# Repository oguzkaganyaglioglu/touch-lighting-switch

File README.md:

# touch-lighting-switch
### Inspect the circuit and decide for yourself whether to use it or not.
### I am not responsible for any damage.

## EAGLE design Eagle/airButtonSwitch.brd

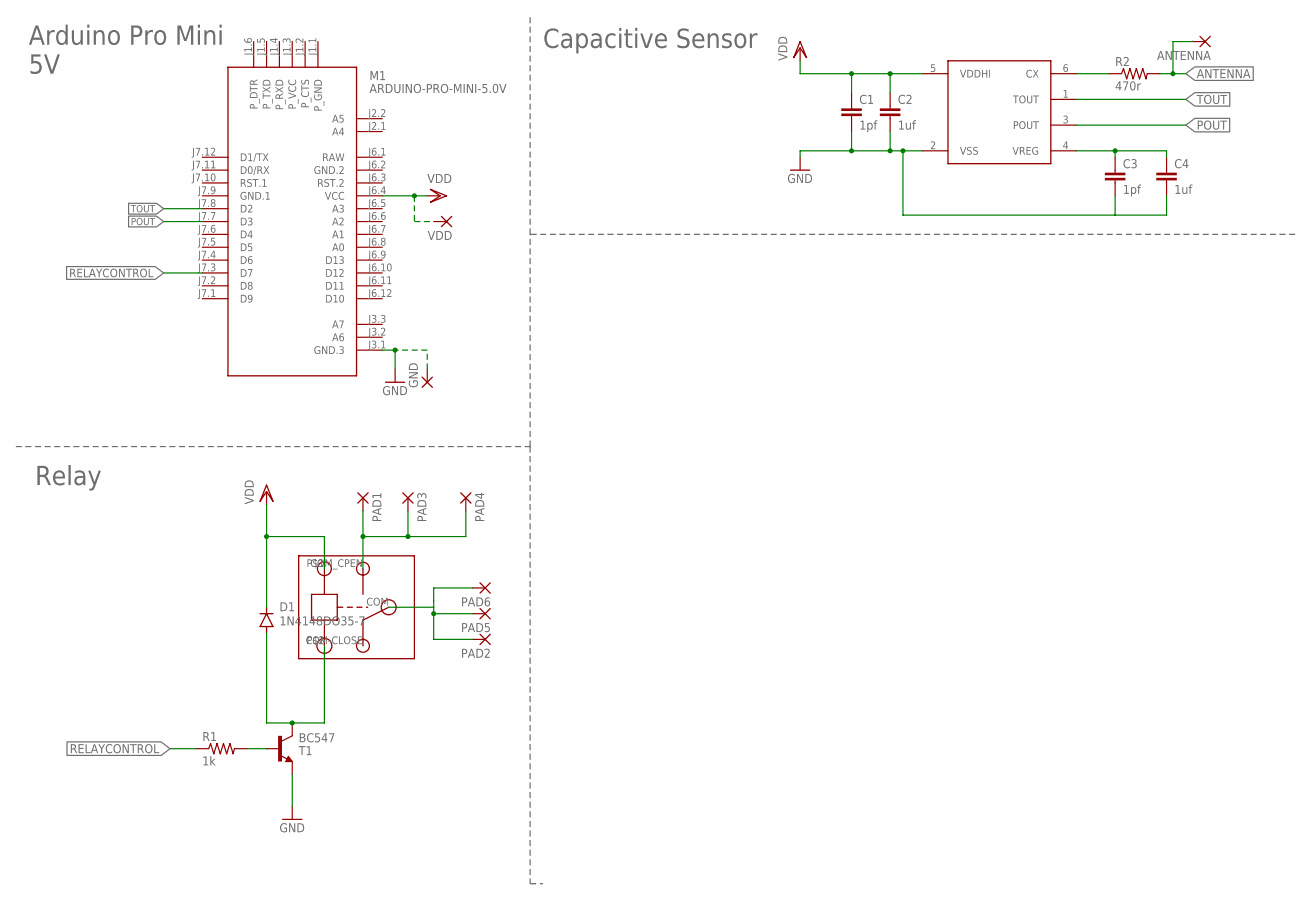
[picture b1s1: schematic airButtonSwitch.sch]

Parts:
ANTENNA: 2,54/1,0
C1, C3: 1pf; C0805
C2, C4: 1uf; C0805
D1: 1N4148DO35-7; DO35-7
GND: 2,54/1,0
M1: ARDUINO-PRO-MINI-5.0V; ARDUINO-PRO-MINI
PAD1, PAD2, PAD3, PAD4, PAD5, PAD6: 2,54/1,0
R1: 1k; 0309/10
R2: 470r; R0805
T1: BC547; TO92
U$1: IQS127D; SOT23-6
U$2: RELAY
VDD: 2,54/1,0

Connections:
ANTENNA: ANTENNA.1, R2.2
GND: C1.2, C2.2, C3.2, C4.2, GND.1, M1.J3.1 (GND.3), T1.1 (E), U$1.2 (VSS)
GND.1: M1.J7.9 (GND.1)
GND.2: M1.J6.2 (GND.2)
unnamed: R1.2, T1.2 (B)
unnamed: D1.A, T1.3 (C), U$2.P$2 (GND)
unnamed: R2.1, U$1.6 (CX)
unnamed: PAD1.1, PAD3.1, PAD4.1, U$2.COM_CPEN (COM-OPEN)
unnamed: C3.1, C4.1, U$1.4 (VREG)
unnamed: PAD2.1, PAD5.1, PAD6.1, U$2.COM
POUT: M1.J7.7 (D3), U$1.3 (POUT)
RAW: M1.J6.1 (RAW)
RELAYCONTROL: M1.J7.3 (D7), R1.1
TOUT: M1.J7.8 (D2), U$1.1 (TOUT)
VDD: C1.1, C2.1, D1.C, M1.J6.4 (VCC), U$1.5 (VDDHI), U$2.P$1 (IN), VDD.1

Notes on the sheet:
Capacitive Sensor
Arduino Pro Mini 5V
Relay

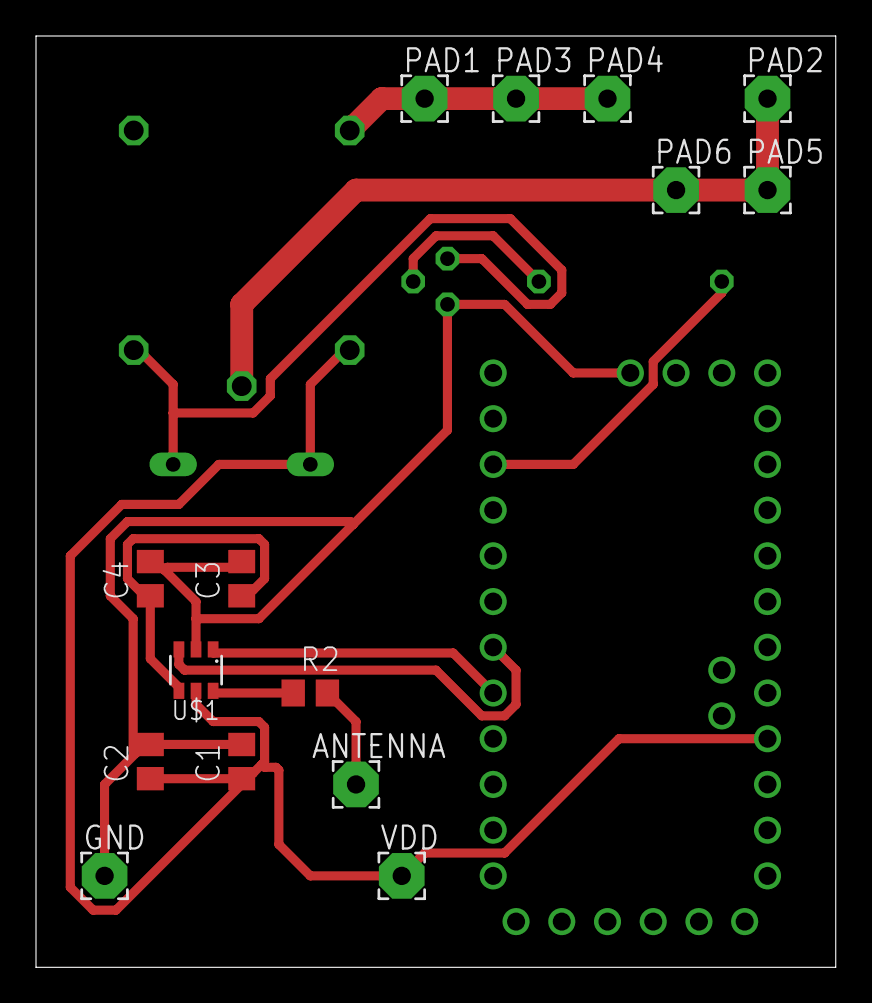
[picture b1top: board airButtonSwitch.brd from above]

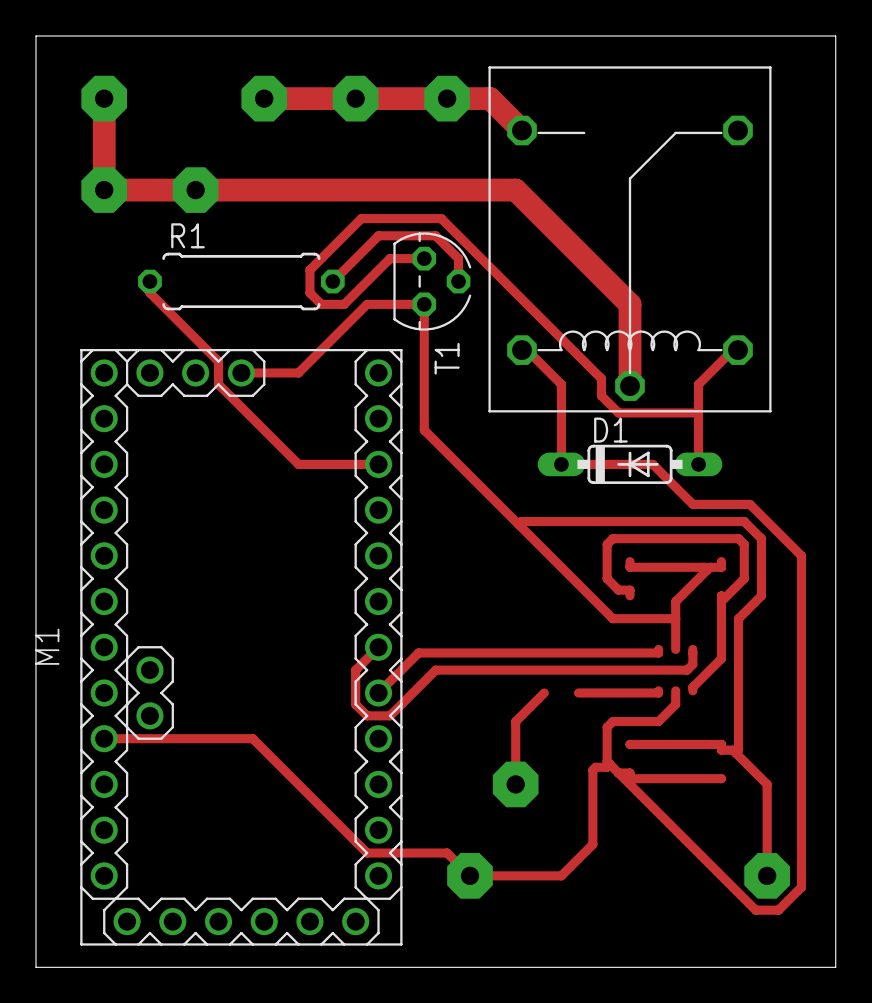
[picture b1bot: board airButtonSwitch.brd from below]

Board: 2 copper layers, 44.4 x 51.7 mm, 20 parts (5 on the bottom side), 12 nets.

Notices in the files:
parts and their libraries:
diy-modules: Released under the Creative Commons Attribution 4.0 International License: http://creativecommons.org/licenses/by/4.0
